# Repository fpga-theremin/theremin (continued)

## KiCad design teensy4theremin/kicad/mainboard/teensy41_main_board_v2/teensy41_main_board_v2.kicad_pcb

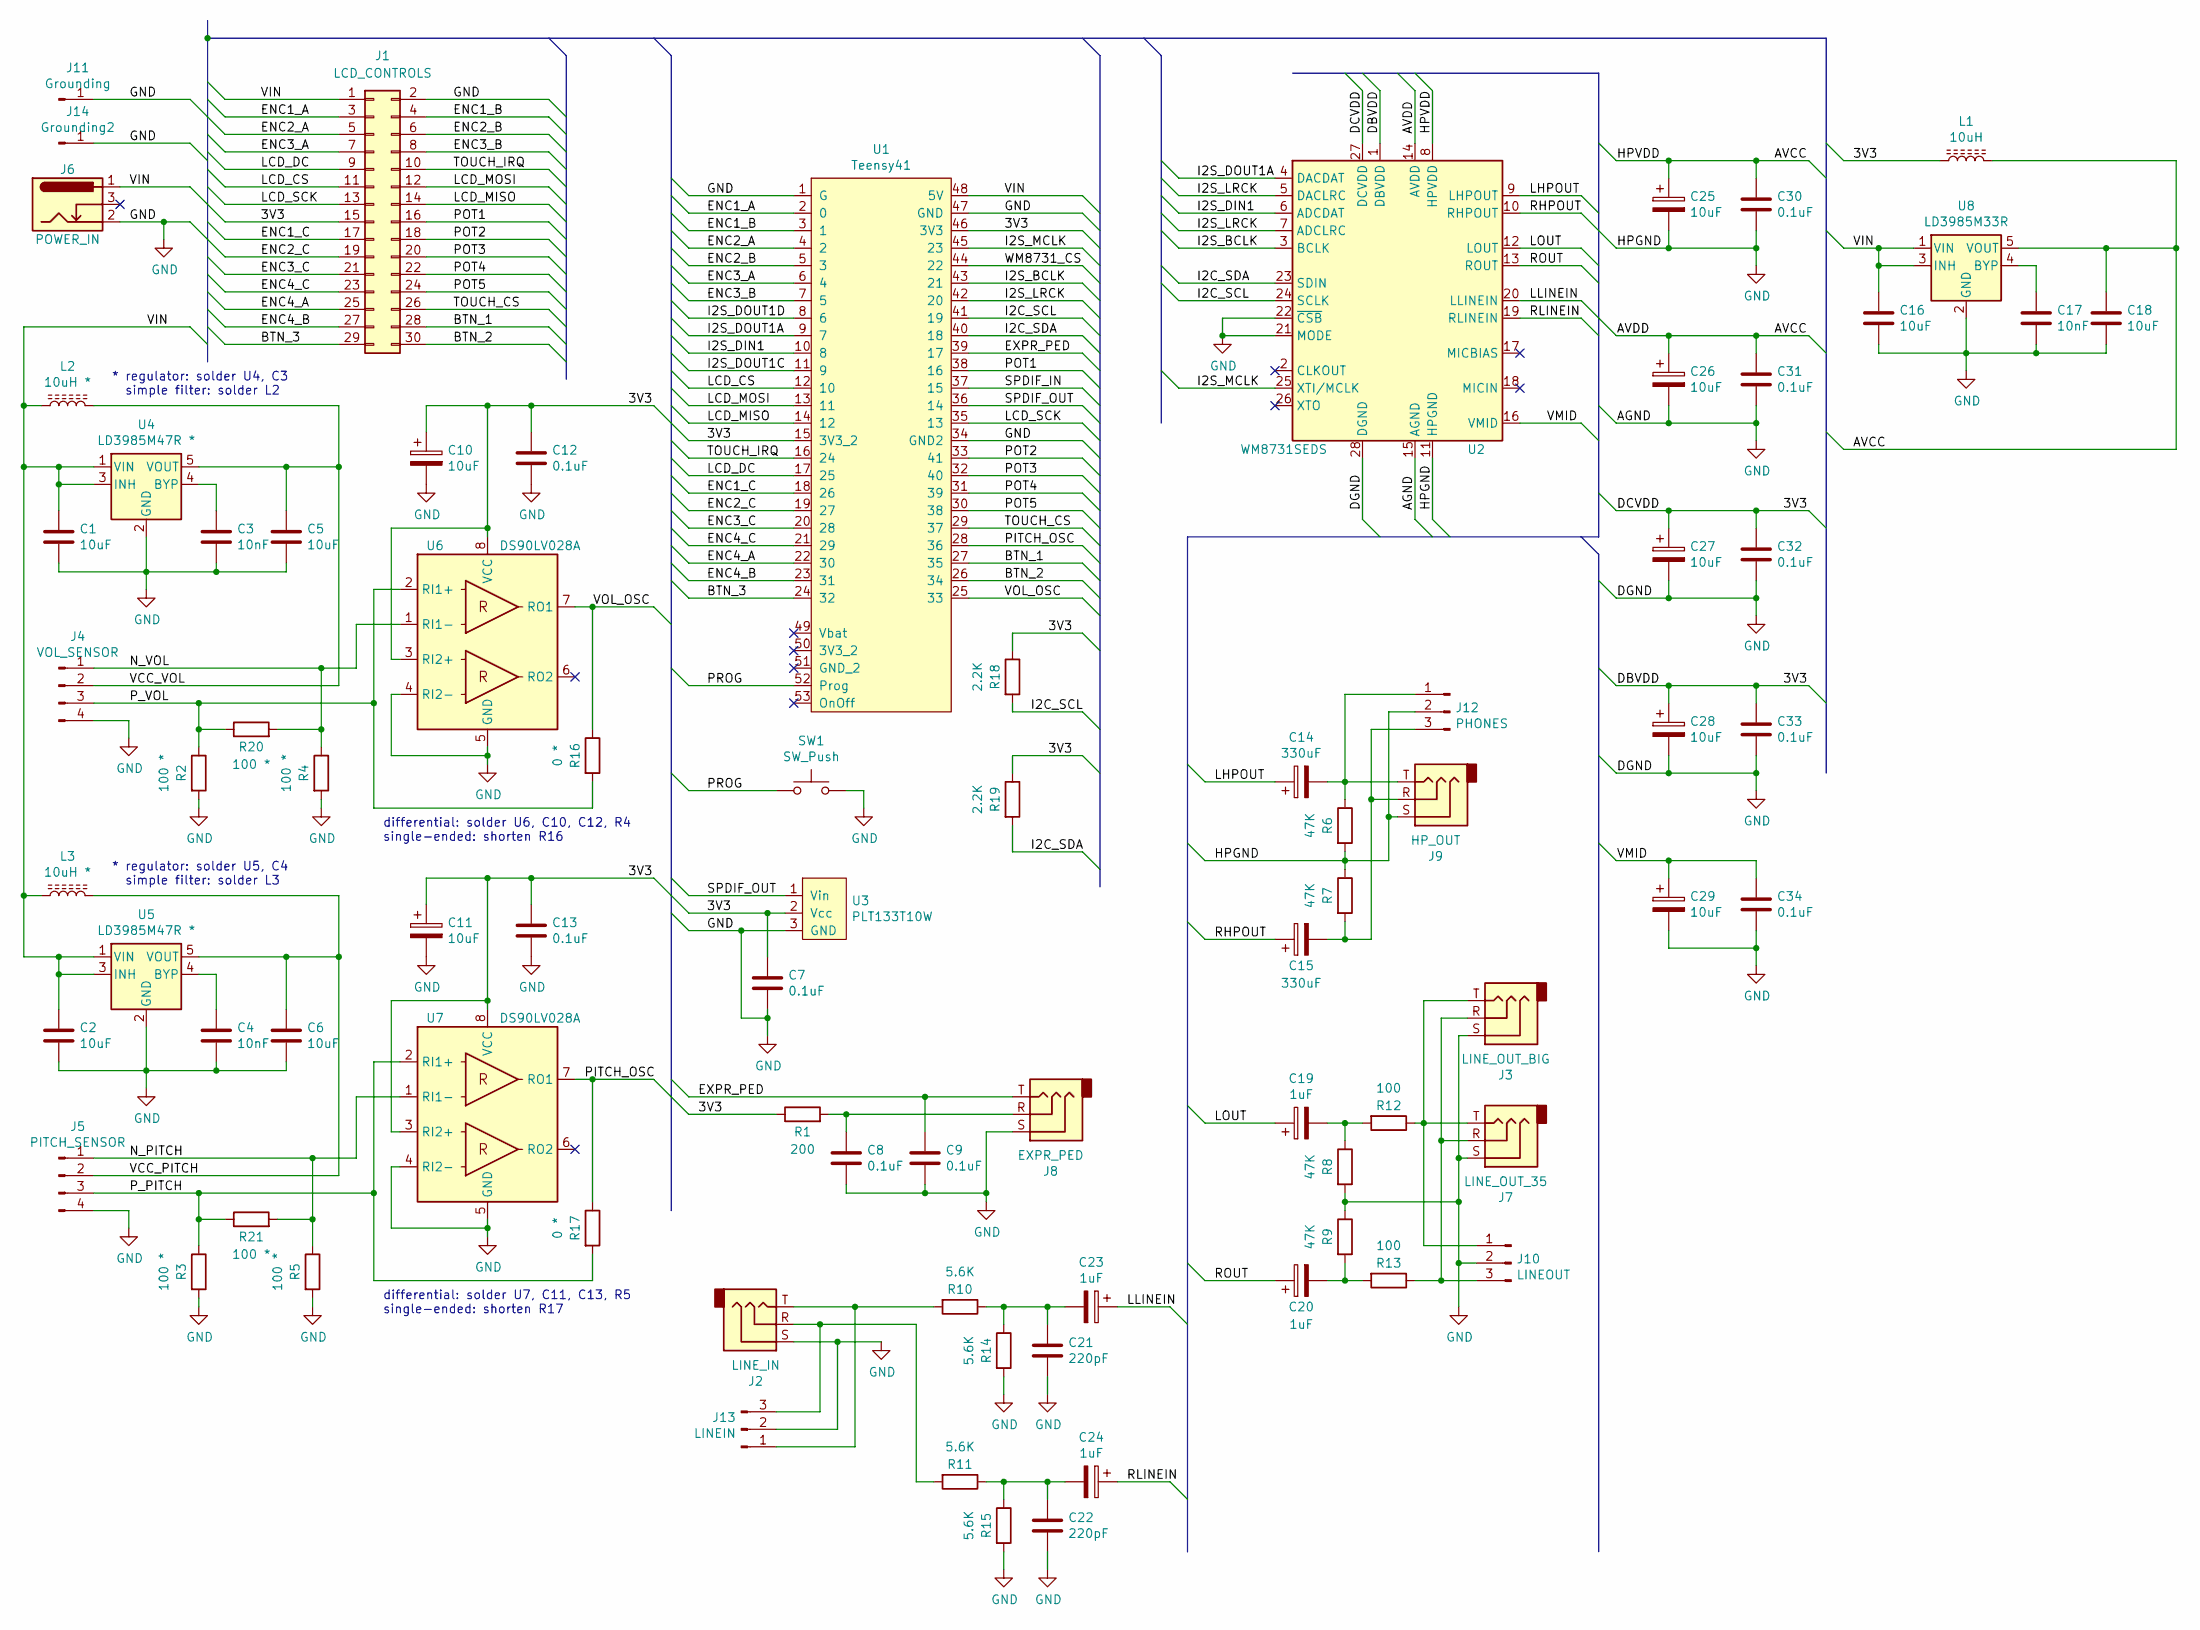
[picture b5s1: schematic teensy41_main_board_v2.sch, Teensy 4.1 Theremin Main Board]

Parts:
C1, C2, C5, C6, C16, C18: 10uF; C_0805_2012Metric_Pad1.18x1.45mm_HandSolder
C3, C4, C17: 10nF; C_0805_2012Metric_Pad1.18x1.45mm_HandSolder
C7, C8, C9, C12, C13, C30, C31, C32, C33, C34: 0.1uF; C_0805_2012Metric_Pad1.18x1.45mm_HandSolder
C10, C11, C25, C26, C27, C28, C29: 10uF; CP_EIA-3216-18_Kemet-A_Pad1.58x1.35mm_HandSolder
C14, C15: 330uF; CP_Radial_D6.3mm_P2.50mm
C19, C20, C23, C24: 1uF; CP_Radial_D5.0mm_P2.00mm
C21, C22: 220pF; C_0805_2012Metric_Pad1.18x1.45mm_HandSolder
J1: LCD_CONTROLS; IDC-Header_2x15_P2.54mm_Vertical
J2: LINE_IN; Jack_3.5mm_CUI_SJ1-3533NG_Horizontal
J3: LINE_OUT_BIG; Jack_6.35mm_ST_008G_04
J4: VOL_SENSOR; PinHeader_1x04_P2.54mm_Horizontal
J5: PITCH_SENSOR; PinHeader_1x04_P2.54mm_Horizontal
J6: POWER_IN; BarrelJack_Wuerth_6941xx301002
J7: LINE_OUT_35; Jack_3.5mm_CUI_SJ1-3533NG_Horizontal
J8: EXPR_PED; Jack_6.35mm_ST_008G_04
J9: HP_OUT; Jack_3.5mm_CUI_SJ1-3533NG_Horizontal
J10: LINEOUT; PinHeader_1x03_P2.54mm_Vertical
J11: Grounding; PinHeader_1x01_P2.54mm_Vertical
J12: PHONES; PinHeader_1x03_P2.54mm_Vertical
J13: LINEIN; PinHeader_1x03_P2.54mm_Vertical
J14: Grounding2; PinHeader_1x01_P2.54mm_Horizontal
L1: 10uH; L_7.3x7.3_H4.5
L2, L3: 10uH *; L_7.3x7.3_H4.5
R1: 200; R_0805_2012Metric_Pad1.20x1.40mm_HandSolder
R2, R3, R4, R5, R20, R21: 100 *; R_0805_2012Metric_Pad1.20x1.40mm_HandSolder
R6, R7, R8, R9: 47K; R_0805_2012Metric_Pad1.20x1.40mm_HandSolder
R10, R11, R14, R15: 5.6K; R_0805_2012Metric_Pad1.20x1.40mm_HandSolder
R12, R13: 100; R_0805_2012Metric_Pad1.20x1.40mm_HandSolder
R16, R17: 0 *; R_0805_2012Metric_Pad1.20x1.40mm_HandSolder
R18, R19: 2.2K; R_0805_2012Metric_Pad1.20x1.40mm_HandSolder
SW1: SW_Push; SW_Tactile_SKHH_Angled
U1: Teensy41
U2: WM8731SEDS; SSOP-28_5.3x10.2mm_P0.65mm
U3: PLT133T10W
U4, U5: LD3985M47R *; SOT-23-5
U6, U7: DS90LV028A; SOIC-8_3.9x4.9mm_P1.27mm
U8: LD3985M33R; SOT-23-5

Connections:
/3V3: C7.1, C10.1, C11.1, C12.1, C13.1, C27.1, C28.1, C32.1, C33.1, J1.15, L1.1, R1.1, R18.1, R19.1, U1.15 (3V3_2), U1.46 (3V3), U2.1 (DBVDD), U2.27 (DCVDD), U3.2 (Vcc), U6.3 (RI2+), U6.8 (VCC), U7.3 (RI2+), U7.8 (VCC)
/AVCC: C18.1, C25.1, C26.1, C30.1, C31.1, L1.2, U2.8 (HPVDD), U2.14 (AVDD), U8.5 (VOUT)
/BTN_1: J1.28, U1.27 (35)
/BTN_2: J1.30, U1.26 (34)
/BTN_3: J1.29, U1.24 (32)
/ENC1_A: J1.3, U1.2 (0)
/ENC1_B: J1.4, U1.3 (1)
/ENC1_C: J1.17, U1.18 (26)
/ENC2_A: J1.5, U1.4 (2)
/ENC2_B: J1.6, U1.5 (3)
/ENC2_C: J1.19, U1.19 (27)
/ENC3_A: J1.7, U1.6 (4)
/ENC3_B: J1.8, U1.7 (5)
/ENC3_C: J1.21, U1.20 (28)
/ENC4_A: J1.25, U1.22 (30)
/ENC4_B: J1.27, U1.23 (31)
/ENC4_C: J1.23, U1.21 (29)
/EXPR_PED: C9.1, J8.T, U1.39 (17)
/I2C_SCL: R18.2, U1.41 (19), U2.24 (SCLK)
/I2C_SDA: R19.2, U1.40 (18), U2.23 (SDIN)
/I2S_BCLK: U1.43 (21), U2.3 (BCLK)
/I2S_DIN1: U1.10 (8), U2.6 (ADCDAT)
/I2S_DOUT1A: U1.9 (7), U2.4 (DACDAT)
/I2S_DOUT1C: U1.11 (9)
/I2S_DOUT1D: U1.8 (6)
/I2S_LRCK: U1.42 (20), U2.5 (DACLRC), U2.7 (ADCLRC)
/I2S_MCLK: U1.45 (23), U2.25 (XTI/MCLK)
/LCD_CS: J1.11, U1.12 (10)
/LCD_DC: J1.9, U1.17 (25)
/LCD_MISO: J1.14, U1.14 (12)
/LCD_MOSI: J1.12, U1.13 (11)
/LCD_SCK: J1.13, U1.35 (13)
/LHPOUT: C14.1, U2.9 (LHPOUT)
/LLINEIN: C23.1, U2.20 (LLINEIN)
/LOUT: C19.1, U2.12 (LOUT)
/N_PITCH: J5.1, R5.1, R21.2, U7.1 (RI1-)
/N_VOL: J4.1, R4.1, R20.2, U6.1 (RI1-)
/PITCH_OSC: R17.1, U1.28 (36), U7.7 (RO1)
/POT1: J1.16, U1.38 (16)
/POT2: J1.18, U1.33 (41)
/POT3: J1.20, U1.32 (40)
/POT4: J1.22, U1.31 (39)
/POT5: J1.24, U1.30 (38)
/PROG: SW1.1, U1.52 (Prog)
/P_PITCH: J5.3, R3.1, R17.2, R21.1, U7.2 (RI1+)
/P_VOL: J4.3, R2.1, R16.2, R20.1, U6.2 (RI1+)
/RHPOUT: C15.1, U2.10 (RHPOUT)
/RLINEIN: C24.1, U2.19 (RLINEIN)
/ROUT: C20.1, U2.13 (ROUT)
/SPDIF_IN: U1.37 (15)
/SPDIF_OUT: U1.36 (14), U3.1 (Vin)
/TOUCH_CS: J1.26, U1.29 (37)
/TOUCH_IRQ: J1.10, U1.16 (24)
/VCC_PITCH: C6.1, J5.2, L3.2, U5.5 (VOUT)
/VCC_VOL: C5.1, J4.2, L2.2, U4.5 (VOUT)
/VIN: C1.1, C2.1, C16.1, J1.1, J6.1, L2.1, L3.1, U1.48 (5V), U4.1 (VIN), U4.3 (INH), U5.1 (VIN), U5.3 (INH), U8.1 (VIN), U8.3 (INH)
/VMID: C29.1, C34.1, U2.16 (VMID)
/VOL_OSC: R16.1, U1.25 (33), U6.7 (RO1)
/WM8731_CS: U1.44 (22)
GND: C1.2, C2.2, C3.2, C4.2, C5.2, C6.2, C7.2, C8.2, C9.2, C10.2, C11.2, C12.2, C13.2, C16.2, C17.2, C18.2, C21.2, C22.2, C25.2, C26.2, C27.2, C28.2, C29.2, C30.2, C31.2, C32.2, C33.2, C34.2, J1.2, J2.S, J3.S, J4.4, J5.4, J6.2, J7.S, J8.S, J9.S, J10.2, J11.1, J12.2, J13.2, J14.1, R2.2, R3.2, R4.2, R5.2, R6.2, R7.1, R8.2, R9.1, R14.2, R15.2, SW1.2, U1.1 (G), U1.34 (GND2), U1.47 (GND), U2.11 (HPGND), U2.15 (AGND), U2.21 (MODE), U2.22 (~CSB), U2.28 (DGND), U3.3 (GND), U4.2 (GND), U5.2 (GND), U6.4 (RI2-), U6.5 (GND), U7.4 (RI2-), U7.5 (GND), U8.2 (GND)
unnamed: C3.1, U4.4 (BYP)
unnamed: C4.1, U5.4 (BYP)
unnamed: C8.1, J8.R, R1.2
unnamed: C14.2, J9.T, J12.1, R6.1
unnamed: C15.2, J9.R, J12.3, R7.2
unnamed: C17.1, U8.4 (BYP)
unnamed: C19.2, R8.1, R12.2
unnamed: C20.2, R9.2, R13.2
unnamed: C21.1, C23.2, R10.1, R14.1
unnamed: C22.1, C24.2, R11.1, R15.1
unnamed: J3.T, J7.T, J10.1, R12.1
unnamed: J3.R, J7.R, J10.3, R13.1
unnamed: J2.T, J13.1, R10.2
unnamed: J2.R, J13.3, R11.2

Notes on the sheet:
* regulator: solder U5, C4 simple filter: solder L3
* regulator: solder U4, C3 simple filter: solder L2
differential: solder U7, C11, C13, R5 single-ended: shorten R17
differential: solder U6, C10, C12, R4 single-ended: shorten R16

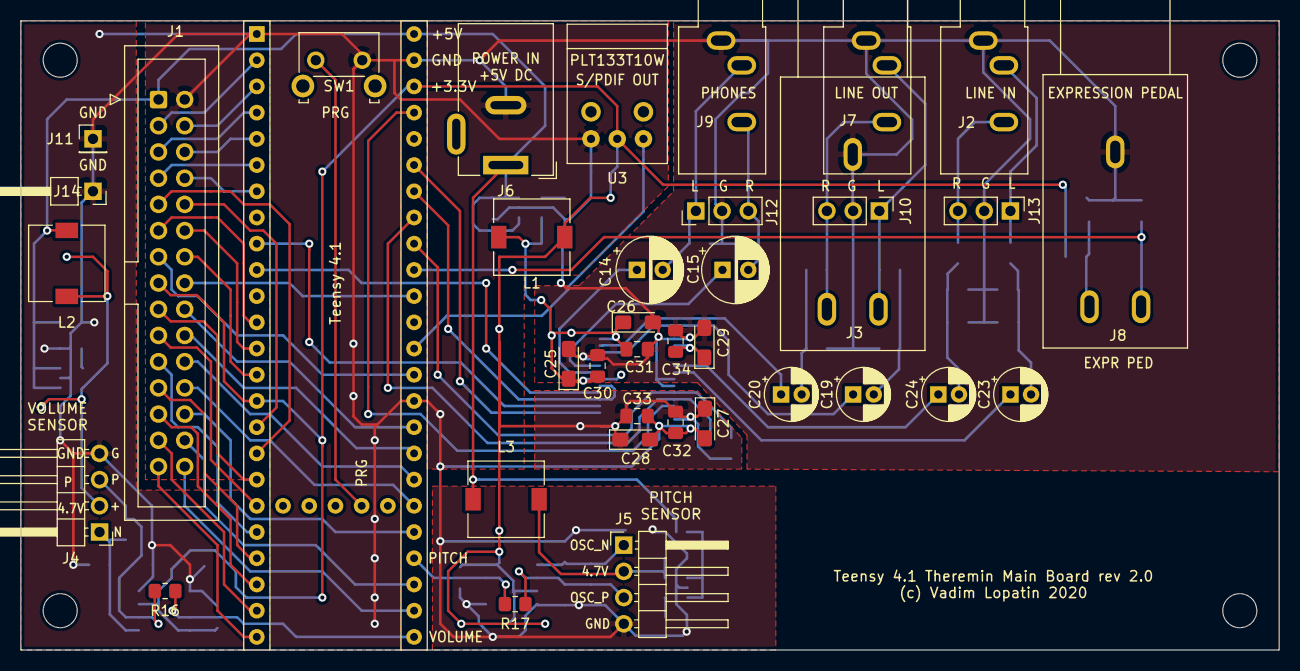
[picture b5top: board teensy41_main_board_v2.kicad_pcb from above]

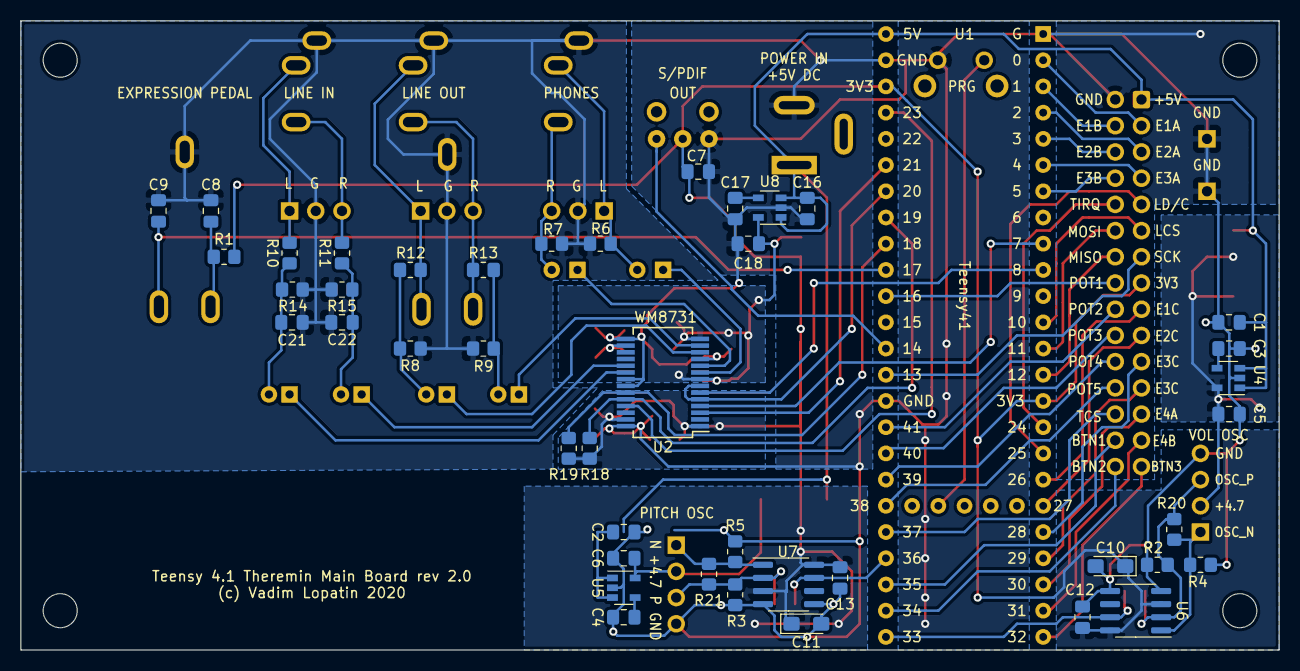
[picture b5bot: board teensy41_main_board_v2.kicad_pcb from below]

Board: 2 copper layers, 121.9 x 61.0 mm, 81 parts (43 on the bottom side), 70 nets.

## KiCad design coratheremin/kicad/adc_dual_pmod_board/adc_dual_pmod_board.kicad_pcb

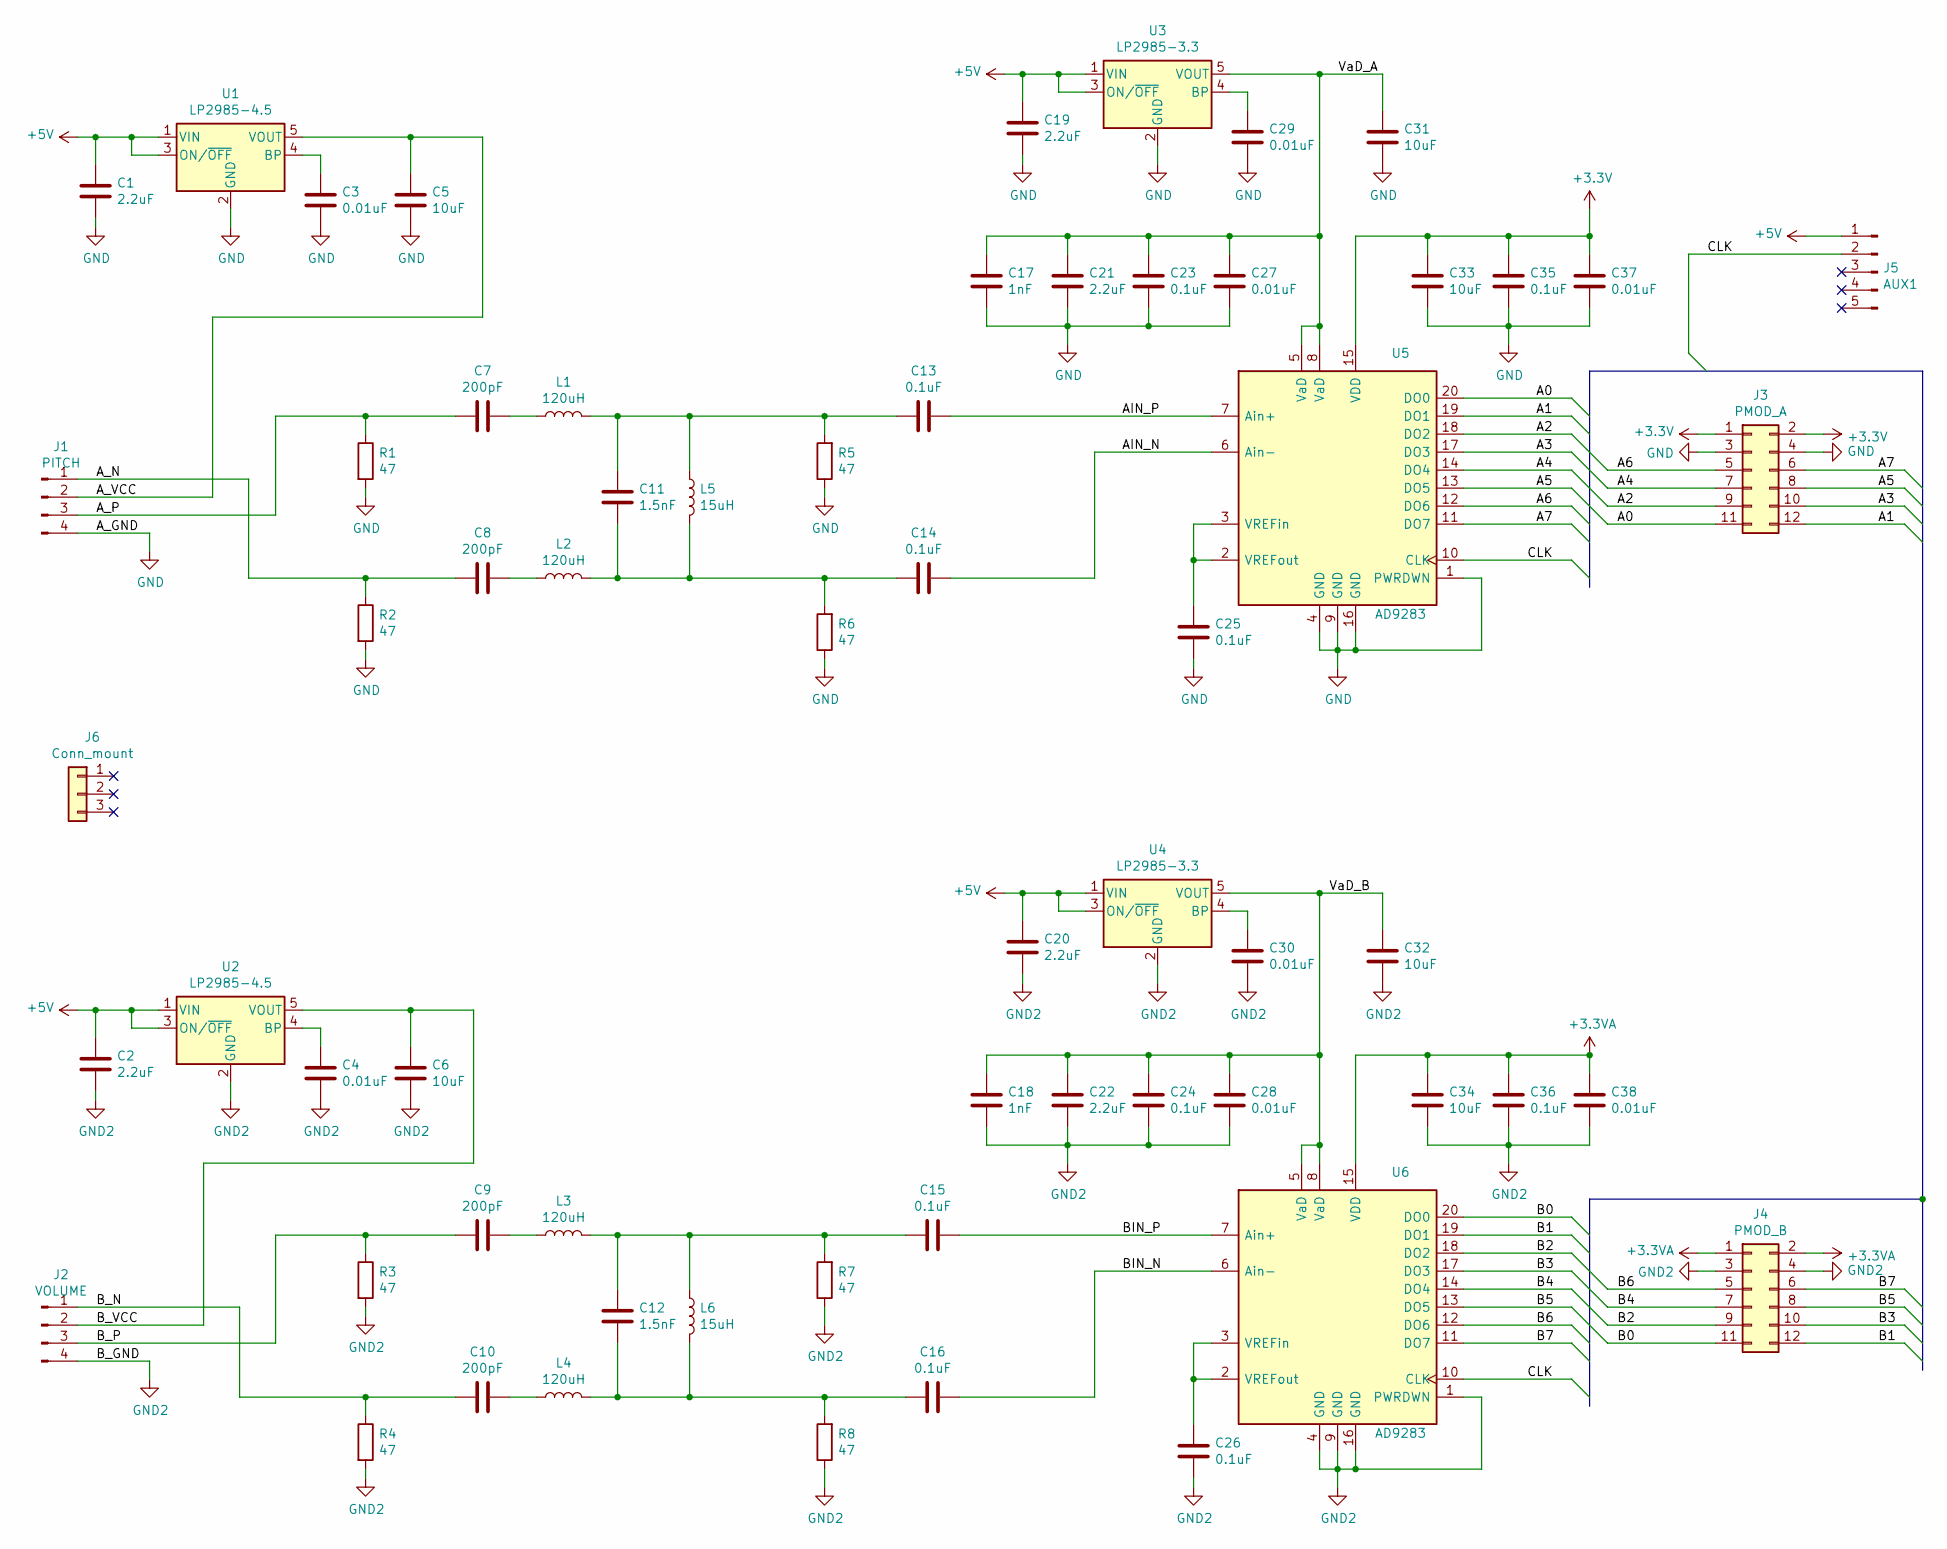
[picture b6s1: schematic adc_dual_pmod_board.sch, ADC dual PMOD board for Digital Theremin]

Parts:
C1, C2, C19, C20, C21, C22: 2.2uF; C_0805_2012Metric_Pad1.18x1.45mm_HandSolder
C3, C4, C27, C28, C29, C30, C37, C38: 0.01uF; C_0805_2012Metric_Pad1.18x1.45mm_HandSolder
C5, C6, C31, C32, C33, C34: 10uF; C_0805_2012Metric_Pad1.18x1.45mm_HandSolder
C7, C8, C9, C10: 200pF; C_0805_2012Metric_Pad1.18x1.45mm_HandSolder
C11, C12: 1.5nF; C_0805_2012Metric_Pad1.18x1.45mm_HandSolder
C13, C14, C15, C16, C23, C24, C25, C26, C35, C36: 0.1uF; C_0805_2012Metric_Pad1.18x1.45mm_HandSolder
C17, C18: 1nF; C_0805_2012Metric_Pad1.18x1.45mm_HandSolder
J1: PITCH; PinHeader_1x04_P2.54mm_Horizontal
J2: VOLUME; PinHeader_1x04_P2.54mm_Horizontal
J3: PMOD_A; PinHeader_2x06_P2.54mm_Horizontal
J4: PMOD_B; PinHeader_2x06_P2.54mm_Horizontal
J5: AUX1; PinSocket_1x05_P2.54mm_Vertical
J6: Conn_mount; PinSocket_1x03_P2.54mm_Vertical
L1, L2, L3, L4: 120uH; L_1210_3225Metric_Pad1.42x2.65mm_HandSolder
L5, L6: 15uH; L_1210_3225Metric_Pad1.42x2.65mm_HandSolder
R1, R2, R3, R4, R5, R6, R7, R8: 47; R_0805_2012Metric_Pad1.20x1.40mm_HandSolder
U1, U2: LP2985-4.5; SOT-23-5
U3, U4: LP2985-3.3; SOT-23-5
U5, U6: AD9283; SSOP-20-wide-7-P0.65

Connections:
+3.3VA: C34.1, C36.1, C38.1, J4.1, J4.2, U6.15 (VDD)
+3V3: C33.1, C35.1, C37.1, J3.1, J3.2, U5.15 (VDD)
+5V: C1.1, C2.1, C19.1, C20.1, J5.1, U1.1 (VIN), U1.3 (ON/~OFF~), U2.1 (VIN), U2.3 (ON/~OFF~), U3.1 (VIN), U3.3 (ON/~OFF~), U4.1 (VIN), U4.3 (ON/~OFF~)
/A0: J3.11, U5.20 (DO0)
/A1: J3.12, U5.19 (DO1)
/A2: J3.9, U5.18 (DO2)
/A3: J3.10, U5.17 (DO3)
/A4: J3.7, U5.14 (DO4)
/A5: J3.8, U5.13 (DO5)
/A6: J3.5, U5.12 (DO6)
/A7: J3.6, U5.11 (DO7)
/AIN_N: C14.1, U5.6 (Ain-)
/AIN_P: C13.1, U5.7 (Ain+)
/A_N: C8.2, J1.1, R2.1
/A_P: C7.2, J1.3, R1.1
/A_VCC: C5.1, J1.2, U1.5 (VOUT)
/B0: J4.11, U6.20 (DO0)
/B1: J4.12, U6.19 (DO1)
/B2: J4.9, U6.18 (DO2)
/B3: J4.10, U6.17 (DO3)
/B4: J4.7, U6.14 (DO4)
/B5: J4.8, U6.13 (DO5)
/B6: J4.5, U6.12 (DO6)
/B7: J4.6, U6.11 (DO7)
/BIN_N: C16.1, U6.6 (Ain-)
/BIN_P: C15.1, U6.7 (Ain+)
/B_N: C10.2, J2.1, R4.1
/B_P: C9.2, J2.3, R3.1
/B_VCC: C6.1, J2.2, U2.5 (VOUT)
/CLK: J5.2, U5.10 (CLK), U6.10 (CLK)
/VaD_A: C17.1, C21.1, C23.1, C27.1, C31.1, U3.5 (VOUT), U5.5 (VaD), U5.8 (VaD)
/VaD_B: C18.1, C22.1, C24.1, C28.1, C32.1, U4.5 (VOUT), U6.5 (VaD), U6.8 (VaD)
GND: C1.2, C3.2, C5.2, C17.2, C19.2, C21.2, C23.2, C25.2, C27.2, C29.2, C31.2, C33.2, C35.2, C37.2, J1.4, J3.3, J3.4, R1.2, R2.2, R5.1, R6.1, U1.2 (GND), U3.2 (GND), U5.1 (PWRDWN), U5.4 (GND), U5.9 (GND), U5.16 (GND)
GND2: C2.2, C4.2, C6.2, C18.2, C20.2, C22.2, C24.2, C26.2, C28.2, C30.2, C32.2, C34.2, C36.2, C38.2, J2.4, J4.3, J4.4, R3.2, R4.2, R7.1, R8.1, U2.2 (GND), U4.2 (GND), U6.1 (PWRDWN), U6.4 (GND), U6.9 (GND), U6.16 (GND)
unnamed: C3.1, U1.4 (BP)
unnamed: C4.1, U2.4 (BP)
unnamed: C7.1, L1.1
unnamed: C8.1, L2.1
unnamed: C9.1, L3.1
unnamed: C10.1, L4.1
unnamed: C11.1, C14.2, L2.2, L5.2, R6.2
unnamed: C11.2, C13.2, L1.2, L5.1, R5.2
unnamed: C12.1, C16.2, L4.2, L6.2, R8.2
unnamed: C12.2, C15.2, L3.2, L6.1, R7.2
unnamed: C25.1, U5.2 (VREFout), U5.3 (VREFin)
unnamed: C26.1, U6.2 (VREFout), U6.3 (VREFin)
unnamed: C29.1, U3.4 (BP)
unnamed: C30.1, U4.4 (BP)

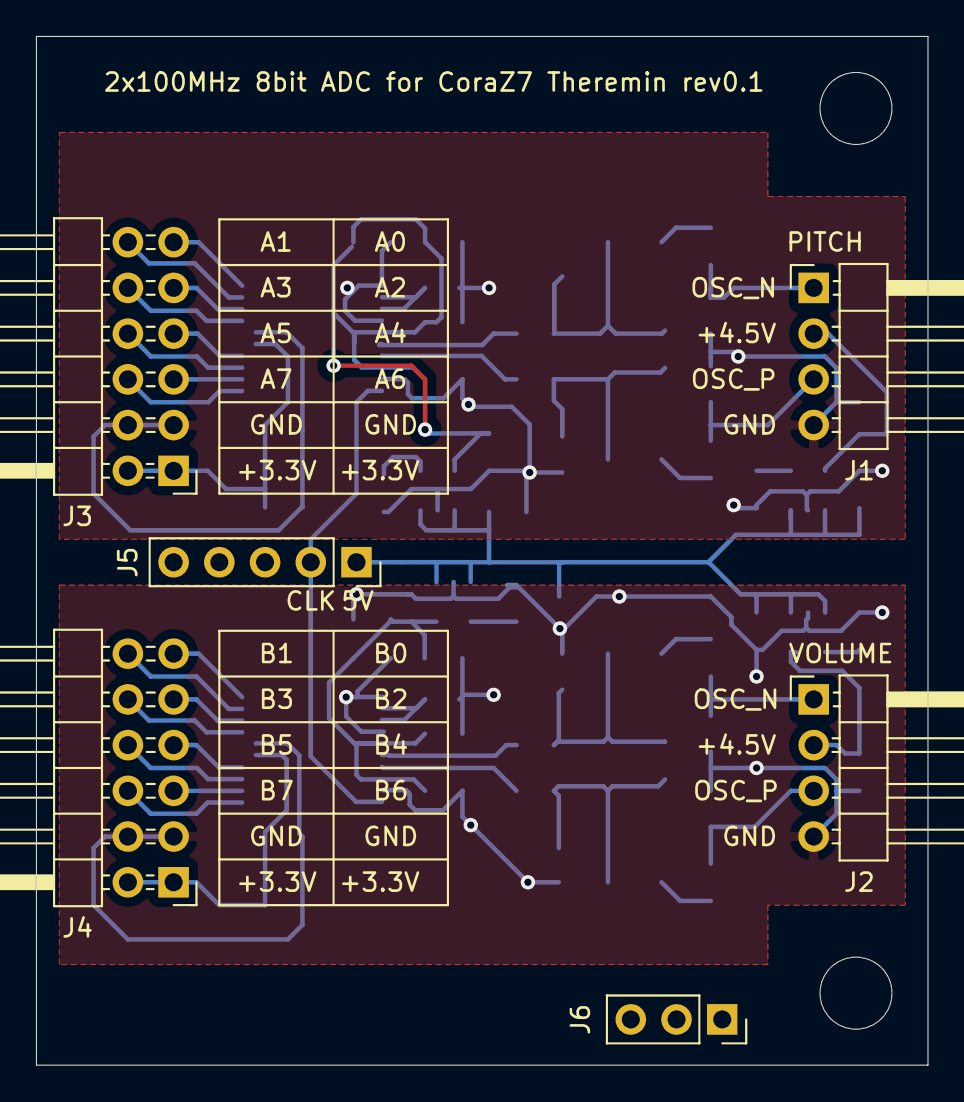
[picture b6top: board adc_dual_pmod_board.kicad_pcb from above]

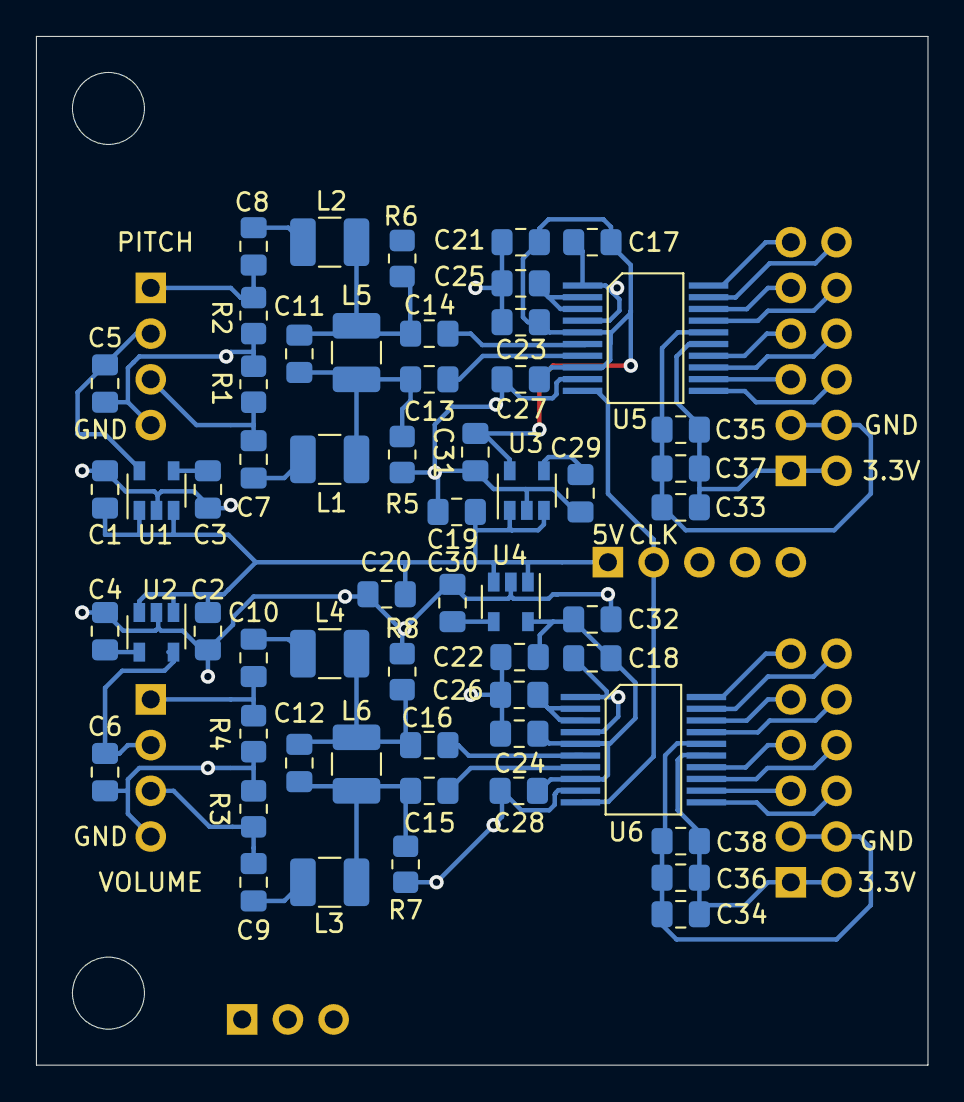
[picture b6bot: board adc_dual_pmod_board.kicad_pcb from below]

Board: 2 copper layers, 49.5 x 57.2 mm, 64 parts (58 on the bottom side), 48 nets.

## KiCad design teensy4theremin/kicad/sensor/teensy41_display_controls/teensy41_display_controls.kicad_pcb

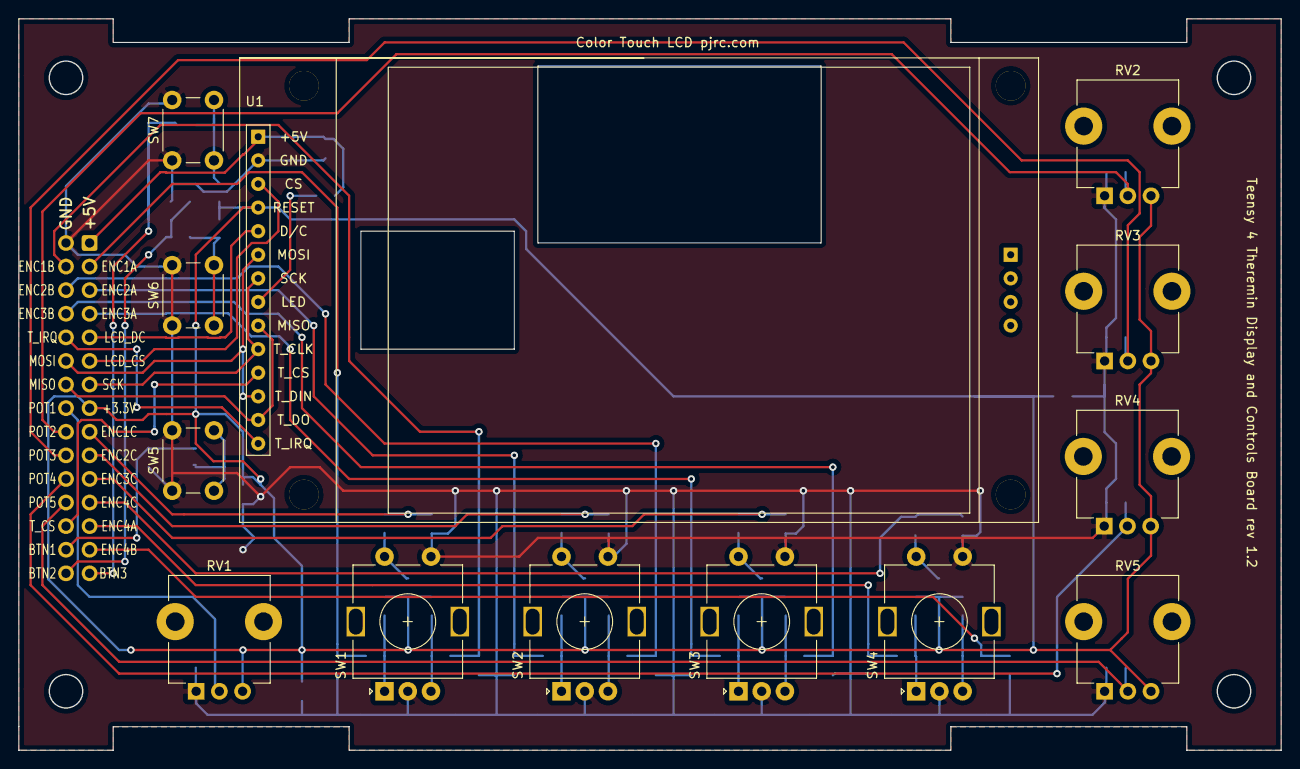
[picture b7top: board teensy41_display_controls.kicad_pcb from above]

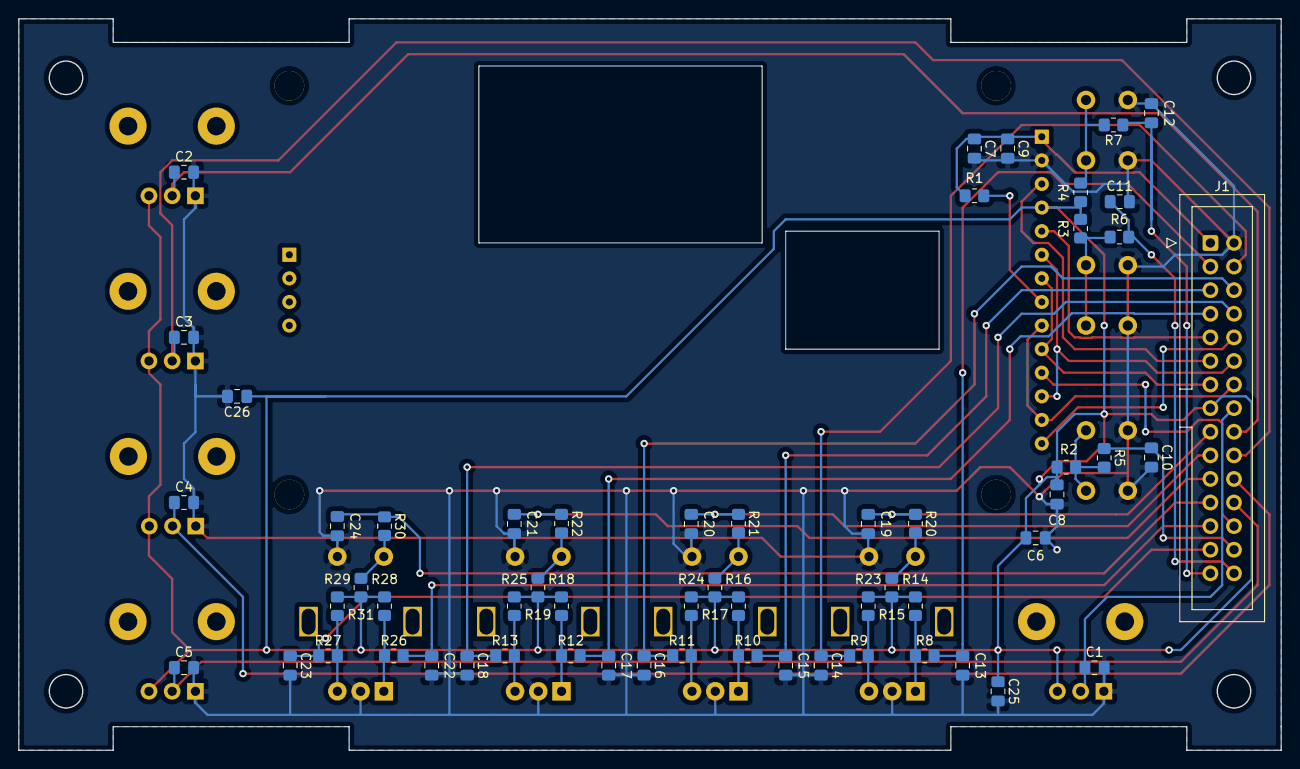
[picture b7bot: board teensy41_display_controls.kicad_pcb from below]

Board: 2 copper layers, 135.8 x 78.6 mm, 71 parts (58 on the bottom side), 46 nets.

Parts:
C1, C2, C3, C4, C5, C8, C9, C25, C26: 0.1uF; C_0805_2012Metric_Pad1.18x1.45mm_HandSolder
C6, C7: 1uF; C_0805_2012Metric_Pad1.18x1.45mm_HandSolder
C10, C11, C12, C13, C14, C15, C16, C17, C18, C19, C20, C21, C22, C23, C24: 0.01uF; C_0805_2012Metric_Pad1.18x1.45mm_HandSolder
J1: MCU_CONN; IDC-Header_2x15_P2.54mm_Vertical
R1: 100; R_0805_2012Metric_Pad1.20x1.40mm_HandSolder
R2, R3, R4, R5, R6, R7, R8, R9, R10, R11, R12, R13, R14, R15, R16, R17, R18, R19, R20, R21, R22, R23, R24, R25, R26, R27, R28, R29, R30, R31: 10K; R_0805_2012Metric_Pad1.20x1.40mm_HandSolder
RV1, RV2, RV3, RV4, RV5: 25K; Potentiometer_TT_P0915N
SW1: ENC1; RotaryEncoder_Alps_EC11E-Switch_Vertical_H20mm
SW2: ENC2; RotaryEncoder_Alps_EC11E-Switch_Vertical_H20mm
SW3: ENC3; RotaryEncoder_Alps_EC11E-Switch_Vertical_H20mm
SW4: ENC4; RotaryEncoder_Alps_EC11E-Switch_Vertical_H20mm
SW5: BTN1; SW_PUSH_6mm_H9.5mm
SW6: BTN2; SW_PUSH_6mm_H9.5mm
SW7: BTN3; SW_PUSH_6mm_H9.5mm
U1: TeensyLCD; TeensyLCD_ILI9341

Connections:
+3V3: C6.1, C8.1, C25.1, C26.1, J1.15, R2.2, R3.2, R4.2, R14.2, R15.1, R16.2, R17.1, R18.2, R19.1, R23.1, R24.1, R25.1, R28.2, R29.1, R31.1, RV1.3, RV2.3, RV3.3, RV4.3, RV5.3, U1.4
+5V: C7.1, C9.1, J1.1, R1.2, U1.1
/BTN1: C10.1, J1.28, R5.1
/BTN2: C11.1, J1.30, R6.1
/BTN3: C12.1, J1.29, R7.1
/ENC1_A: C13.2, J1.3, R8.2
/ENC1_B: C14.1, J1.4, R9.1
/ENC1_C: C19.2, J1.17, R20.1
/ENC2_A: C15.2, J1.5, R10.2
/ENC2_B: C16.1, J1.6, R11.1
/ENC2_C: C20.2, J1.19, R21.1
/ENC3_A: C17.2, J1.7, R12.2
/ENC3_B: C18.1, J1.8, R13.1
/ENC3_C: C21.2, J1.21, R22.1
/ENC4_A: C22.2, J1.25, R26.2
/ENC4_B: C23.1, J1.27, R27.1
/ENC4_C: C24.2, J1.23, R30.1
/LCD_CS: J1.11, U1.3
/LCD_DC: J1.9, U1.5
/MISO: J1.14, U1.9, U1.13
/MOSI: J1.12, U1.6, U1.12
/POT1: C1.1, J1.16, RV1.2
/POT2: C2.1, J1.18, RV2.2
/POT3: C3.1, J1.20, RV3.2
/POT4: C4.1, J1.22, RV4.2
/POT5: C5.1, J1.24, RV5.2
/SCK: J1.13, U1.7, U1.10
/T_CS: J1.26, U1.11
/T_IRQ: J1.10, U1.14
GND: C1.2, C2.2, C3.2, C4.2, C5.2, C6.2, C7.2, C8.2, C9.2, C10.2, C11.2, C12.2, C13.1, C14.2, C15.1, C16.2, C17.1, C18.2, C19.1, C20.1, C21.1, C22.1, C23.2, C24.1, C25.2, C26.2, J1.2, RV1.1, RV2.1, RV3.1, RV4.1, RV5.1, SW1.C, SW1.S1, SW2.C, SW2.S1, SW3.C, SW3.S1, SW4.C, SW4.S1, SW5.1, SW6.1, SW7.1, U1.2
unnamed: R1.1, U1.8
unnamed: R2.1, R5.2, SW5.2
unnamed: R3.1, R6.2, SW6.2
unnamed: R4.1, R7.2, SW7.2
unnamed: R10.1, R16.1, SW2.A
unnamed: R11.2, R17.2, SW2.B
unnamed: R12.1, R18.1, SW3.A
unnamed: R13.2, R19.2, SW3.B
unnamed: R8.1, R14.1, SW1.A
unnamed: R9.2, R15.2, SW1.B
unnamed: R20.2, R23.2, SW1.S2
unnamed: R21.2, R24.2, SW2.S2
unnamed: R22.2, R25.2, SW3.S2
unnamed: R26.1, R28.1, SW4.A
unnamed: R27.2, R29.2, SW4.B
unnamed: R30.2, R31.2, SW4.S2

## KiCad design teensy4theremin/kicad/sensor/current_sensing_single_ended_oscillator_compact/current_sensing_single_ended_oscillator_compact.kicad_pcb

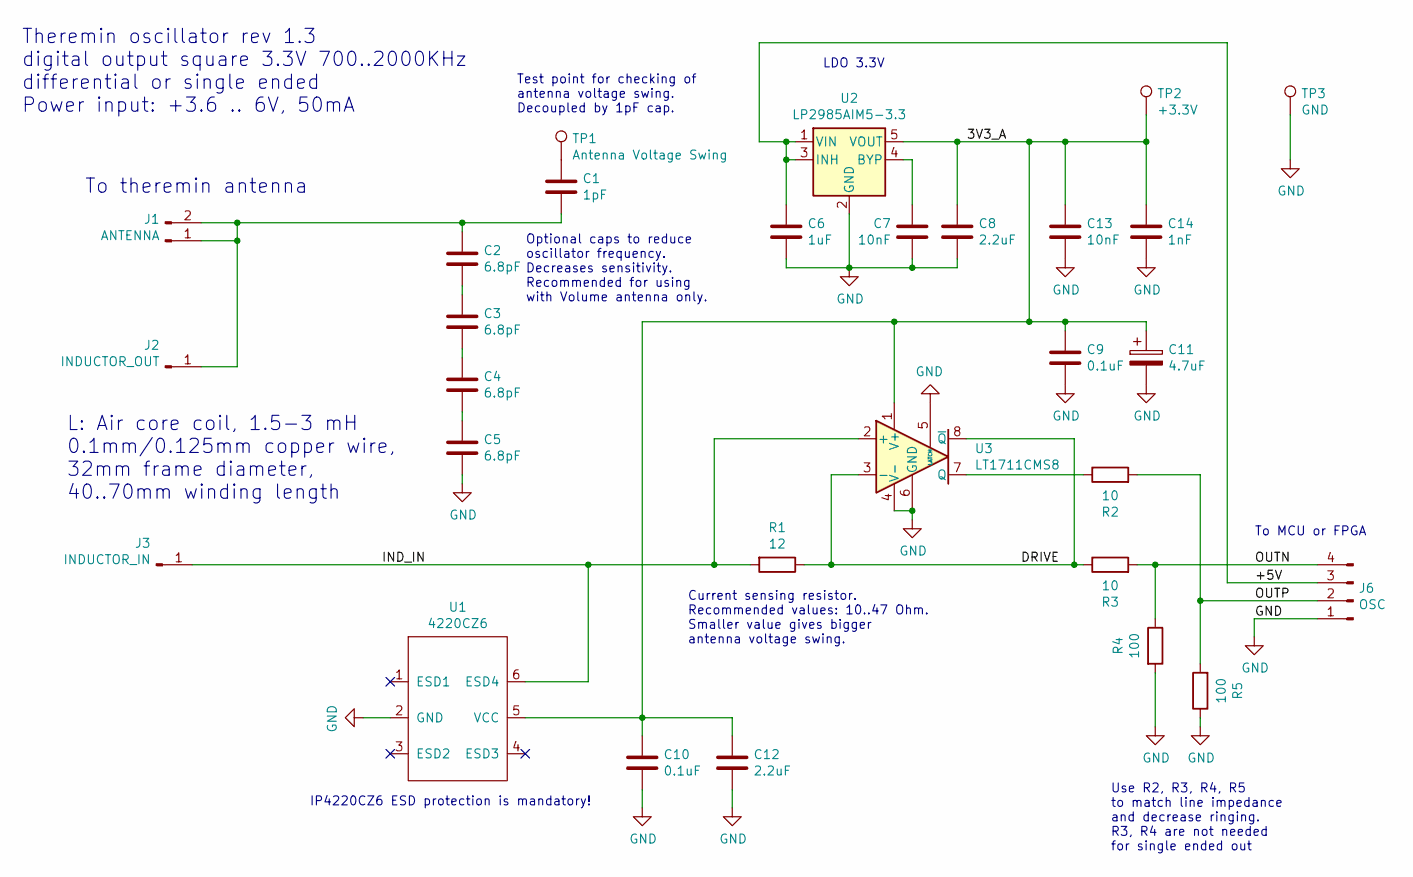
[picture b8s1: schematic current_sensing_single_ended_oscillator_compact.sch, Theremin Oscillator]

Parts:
C1: 1pF; C_0805_2012Metric_Pad1.15x1.40mm_HandSolder
C2, C3, C4, C5: 6.8pF; C_0805_2012Metric_Pad1.15x1.40mm_HandSolder
C6: 1uF; C_0805_2012Metric_Pad1.15x1.40mm_HandSolder
C7, C13: 10nF; C_0805_2012Metric_Pad1.15x1.40mm_HandSolder
C8, C12: 2.2uF; C_0805_2012Metric_Pad1.15x1.40mm_HandSolder
C9, C10: 0.1uF; C_0805_2012Metric_Pad1.15x1.40mm_HandSolder
C11: 4.7uF; CP_EIA-3528-21_Kemet-B_Pad1.50x2.35mm_HandSolder
C14: 1nF; C_0805_2012Metric_Pad1.15x1.40mm_HandSolder
J1: ANTENNA; PinHeader_1x02_P2.54mm_Horizontal
J2: INDUCTOR_OUT; PinHeader_1x01_P2.54mm_Horizontal
J3: INDUCTOR_IN; PinHeader_1x01_P2.54mm_Horizontal
J6: OSC; PinHeader_1x04_P2.54mm_Horizontal
R1: 12; R_0805_2012Metric_Pad1.20x1.40mm_HandSolder
R2, R3: 10; R_0805_2012Metric_Pad1.20x1.40mm_HandSolder
R4, R5: 100; R_0805_2012Metric_Pad1.20x1.40mm_HandSolder
TP1: Antenna Voltage Swing; PinHeader_1x01_P1.27mm_Vertical
TP2: +3.3V; PinHeader_1x01_P1.27mm_Vertical
TP3: GND; PinHeader_1x01_P1.27mm_Vertical
U1: 4220CZ6; TSOP-6_1.65x3.05mm_P0.95mm
U2: LP2985AIM5-3.3; SOT-23-5
U3: LT1711CMS8; MSOP-8_3x3mm_P0.65mm

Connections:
/3V3_A: C8.1, C9.1, C10.1, C11.1, C12.1, C13.1, C14.1, TP2.1, U1.5 (VCC), U2.5 (VOUT), U3.1 (V+)
/5V: C6.1, J6.3, U2.1 (VIN), U2.3 (INH)
/DRIVE: R1.1, R3.1, U3.3 (-), U3.8 (~Q)
/IND_IN: J3.1, R1.2, U1.6 (ESD4), U3.2 (+)
/OUTN: J6.4, R3.2, R4.1
/OUTP: J6.2, R2.2, R5.2
GND: C5.2, C6.2, C7.2, C8.2, C9.2, C10.2, C11.2, C12.2, C13.2, C14.2, J6.1, R4.2, R5.1, TP3.1, U1.2 (GND), U2.2 (GND), U3.4 (V-), U3.5 (LATCH), U3.6 (GND)
unnamed: C1.1, TP1.1
unnamed: C1.2, C2.1, J1.1, J1.2, J2.1
unnamed: C2.2, C3.1
unnamed: C3.2, C4.1
unnamed: C4.2, C5.1
unnamed: C7.1, U2.4 (BYP)
unnamed: R2.1, U3.7 (Q)

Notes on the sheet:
To theremin antenna
Theremin oscillator rev 1.3 digital output square 3.3V 700..2000KHz differential or single ended Power input: +3.6 .. 6V, 50mA
L: Air core coil, 1.5-3 mH 0.1mm/0.125mm copper wire, 32mm frame diameter, 40..70mm winding length
IP4220CZ6 ESD protection is mandatory!
LDO 3.3V
To MCU or FPGA
Optional caps to reduce oscillator frequency. Decreases sensitivity. Recommended for using with Volume antenna only.
Test point for checking of antenna voltage swing. Decoupled by 1pF cap.
Current sensing resistor. Recommended values: 10..47 Ohm. Smaller value gives bigger antenna voltage swing.
Use R2, R3, R4, R5 to match line impedance and decrease ringing. R3, R4 are not needed for single ended out
